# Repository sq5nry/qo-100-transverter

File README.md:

# qo-100-transverter

*[Wersja polska / Polish version](README_PL.md)*

## What it's about
- source-available, hardware and software project of a transverter for the [QO-100](https://amsat-uk.org/satellites/geo/eshail-2/) satellite. The outdoor version takes 1.5 days to assemble starting from bare PCB, bag of parts, and patience.
- complete up and down-converter below 199,99 € : [see the BOM](hw-trv/BOM.md)
- in-fab assembly automation in progress (*v0.3-snapshot*)

## Equipment and skills required
- knack for SMD soldering with stencil and solder paste
- patience for by-hand component placement
- 10x10 cm heat plate and ability to control the temperature profile
- multimeter
- set of fixed attenuators, a variable one and patch cables
- VNA+SA and a signal generator up to 3GHz minimum
- Pluto-like SDR to receive, measure, and generate signals during tests and adjustments
- RF power meter
- 30V 5A lab power supply with over-current protection
- ST-link programmer
- patience for drilling holes in aluminum enclosure
- patience for tapping 3 mm holes
- RF personal protective equipment rated to attenuate 2.4 GHz frequencies

## Features
- QO-100 narrow-band transponder SSB, CW, and Data operation with an HF-VHF transceiver
- ±0.25 ppm reference oscillator stability
- 6W of 2.4GHz output power
- 10m, 6m, 4m, 2m, 70cm bands supported, 5W input power maximum
- 738MHz filtered, receive output for signal supervision
- 25MHz reference oscillator for LNB: injected into the LNB feeder or the shared output
- PTT-over-coax supported
- splash-proof outdoor version

## Block diagram

## Operation

### Prerequisites

- 28V DC power supply offering 1.1A (31W), or
- 13.8V DC at 3.5A and using the Companion Box for voltage boost
- 60cm dish antenna suggested with 5W ERP according to AMSAT guidelines
- standard universal LNB (13/18V), 500mA fused
- standard PTT ground-to-transmit, or
- PTT-over-coax by transceiver or using the Companion Box to mix PTT and RF
- operation from 13.8V (1.1A) directly is possible with lower output power (2W max). Adequate linearity is not guaranteed.

### Basic procedures

1. Configure IF (Intermediate Frequency) corresponding to your transceiver setup using the three-position slide switch to select one of eight possible IF base frequencies.
2. IF can be updated on-the-fly, the change is indicated by a flashing green LED.
3. Connect DC power and PTT signal.
4. Switch on RX pre-amp in your transceiver.
5. Check the position of the received QO-100 mid beacon, adjust it to fall into the middle of the band using REF ADJ control with a small flat-head screwdriver.
6. Set your transceiver output power to 3–5W and adjust TX ATT control so that your signal is at the mid-beacon level. Lower power with a higher TX ATT setting is advised to minimize heat dissipation inside the transverter.

## Schematics

- [v0.3 schematics (current)](hw-trv/sch_v0.3-sh.pdf)
- [v0.2 schematics](https://github.com/sq5nry/qo-100-transverter/blob/77cc88346982ab3cb6913bec3531f18df363a01a/hw-trv/sch_v0.2.pdf) — release presented at [Ham Radio Friedrichshafen 2026](https://www.hamradio-friedrichshafen.com/trade-show-program/exhibitors/exhibitor?id=107515806) in [PZK](https://www.pzk.org.pl/) (Polish Amateur Radio Union) tent

> **⚠️ Note:** do not mount the OCXO subcircuit (error amplifier and heater components, connected via JP5). This circuitry is non-functional in the current release and will be removed in a future revision. The freed board space can instead be used for additional thermal insulation around the TCXO.

## Assembly

### Preparation

Gather all parts from the [BOM](hw-trv/BOM.md) and arrange them on your workbench before starting.
Verify IC orientation markings and keep ESD-sensitive parts (ICs, MOSFETs) in their packaging
until placement.

### Solder paste application

Apply solder paste through the PCB stencil. Two paste options have been tested:

- **Sn63Pb37** (183°C eutectic, e.g. Mechanic XG-50) — recommended; standard SnPb profile,
  widely available, easy to work with.
- **Sn42Bi58** (~138°C eutectic, e.g. ChipQuik SMD291 or Mechanic UV50) — low-melting-point
  alternative; useful if heat-sensitive components are a concern, but requires careful handling
  as bismuth alloys are more brittle and less compatible with lead-containing component finishes.

Clamp the stencil firmly over the PCB, apply paste with a squeegee in a single smooth stroke,
and lift the stencil straight up to avoid smearing. Inspect paste deposits under magnification
before placing components.

### Component placement

Place all SMD components onto the paste deposits. Work from smallest to largest — passives first,
then ICs. Pay close attention to pin-1 orientation on all ICs and polarised components.
QFN packages require careful centring over their pads; the paste surface tension will self-align
them slightly during reflow.

### Reflow

Place the populated PCB on the heat plate. Follow a standard **SnPb reflow profile**:

| Zone | Temperature | Duration |
|------|------------|---------|
| Preheat | 100–150°C | ~60 s |
| Soak | 150–180°C | 60–90 s |
| Reflow (above liquidus) | 183–215°C peak | 30–45 s |
| Cooldown | ramp down | natural |

Use hot air to assist reflow around QFN packages and larger thermal-mass parts (PA, DC-DC
converter). Watch for bridging on fine-pitch ICs.

### Inspection and rework

After reflow and cooldown, inspect all joints under magnification:

- Remove solder bridges with braid or a fine soldering iron tip.
- Add solder to any under-filled joints, particularly on exposed thermal pads of QFN/PQFN
  packages — use a soldering iron with flux through the heat-via holes on the bottom side.
- The bottom-side thermal vias do not need to be flush; they will be covered by thermal pads
  connecting to the heat spreader or enclosure floor.

### Through-hole parts

Solder the 5W power resistor by hand after SMD reflow. Mount the TCVCXO with polyester
tape and foam fitting as described in the enclosure assembly notes.

### EMI shields

The PCB has footprints for SMD metal EMI shields over sensitive sections. Mounting the shield over the IF Unit is important for stability. Shielding the switched-mode power supply section and TCXO is recommended but not critical.

### EMI absorber

Most of enclosure types require absorption foams in PA area to help suppress self-oscillations and minimize parasitic coupling between stages. The amplifier may start self-oscillations at a frequency between 2.2-2.5GHz with full power without the absorber. \
See gallery section for a poor's-man approach.

### PCB cleaning

Wash the assembled PCB thoroughly with isopropanol to remove all flux residues before
proceeding. Flux contamination on the board surface can significantly affect 2.4GHz circuit
behaviour — altering tuning, increasing losses, and making RF adjustments unreliable.
Allow the board to dry completely before applying power.

### Power-up and initial checks

Connect power and PTT cables. Supply 28V with the current limit set to 50mA. Measure the
following test points and verify voltages before proceeding:

1. Check 13V and 5V test points first.
2. If those are correct, verify: 3V (analog), 3V (digital), 3.3V (reference oscillator),
   3V (MCU), 9V, and 1.8V.

If any rail is missing or out of range, do not proceed — investigate before applying full power.

### Firmware

Flash the firmware using **STM32CubeProgrammer** via the ST-LINK interface and the SWD ISP
header. A firmware release binary is provided; to build from source use **STM32CubeIDE**.

After programming, the **PLL LOCK** indicator should illuminate. If it does not, check the
25MHz reference oscillator signal.

### PA bias adjustment

Set the quiescent drain current (Idq) for the 2.4GHz PA stages:

- 1st stage: **15mA**
- 2nd stage: **75mA**

Before adjusting, raise the lab supply's overload protection (current limit) to about
**250mA** so it does not trip during bias trimming.

To measure Idq, cut the respective drain supply PCB trace and insert an ammeter in series or just calculate current delta on the lab supply.
Adjust the bias trimmer for each stage until the target Idq is reached, then bridge the cut
with solder.
Adjust the position of C87 in the PA output circuit for highest stage gain.

### PA gain and output matching

Measure the PA gain and adjust the position of C88 to obtain **28–30dB** gain — slide C88 along the output line toward the thicker section. If that alone does not maximise gain, add 0.8pF in parallel with C88. Do not mount
the low-pass filter (LPF) elements yet — bridge the LPF inductor footprint with a strip of
copper foil instead, so the PA output can be measured without the potentially mismatched filter.

Once the gain is set, mount the LPF inductor and adjust it for a maximum insertion loss of
**1dB at 2.4GHz**.

Set the overload (overcurrent) protection threshold to **1.1A**.

Connect an RF power meter to the 2.4GHz TX output socket and adjust the TX path for **6W**
output across your expected input power range (1–5W).

> **⚠️ Warning:** do not increase input power in an attempt to reach 6W until PA gain is at least 28dB. PA chip will overheat and operate non-linearly. I bricked one PA after overloading its input with just 17dBm.

> **⚠️ Warning:** do not drive the PA past **9..12W** output — exceeding this limit pushes the
> stage into non-linear operation, causing spectral splatter and interference to other users.

> **⚠️ Note:** the PA chip tolerates antenna mismatch well — SWR up to 10:1 on the 2.4GHz
> TX port will not damage it. However, operating with no load connected may cause
> self-oscillation in the 2.2–2.5GHz range; the on-board 1.5A resettable fuse will limit
> the resulting current in that event.

## Circuit description

### Transmit path

The transceiver signal (up to 5W / +37dBm) passes through a variable 35–42dB attenuator,
reducing it to approximately −8dBm at the mixer input. A diode protection limiter with a
clipping level starting softly at +4dBm guards the mixer — this is to limit damage in case you connect 100W for a longer time. Note that sustained high-power overshoots may still damage the PA by exceeding its maximum input level even if the mixer itself survives. \
The signal enters a balanced Gilbert-cell mixer (RFFC2071). The mixer's wideband 4:1 output transformer provides differential symmetry that helps cancel LO leakage, minimising it before the signal
even reaches the downstream filter. Although slightly more expensive than a narrowband balun
chip, the wideband transformer's superior symmetry keeps LO leakage below −32dBc relative
to the upper sideband with only two SAW filters — most critically on the 29MHz band, where
LO leakage lands closest to occupied spectrum. The TX mixer on 10m is intentionally operated at a reduced bias current, which directly reduces LO leakage at its output. \
The output is filtered by a 2.4GHz bandpass filter to further suppress any residual LO leakage and the image frequency. The two TX bandpass filters are inter-stage matched using a parallel 0.8pF capacitor; this matching network optimises power transfer between the filter sections. A driver stage amplifies the signal to +12dBm, followed by a 29dB LDMOS power amplifier — whose input is matched to 50Ω using a short high-impedance transmission line — and a low-pass filter, delivering +38dBm (6W) to
the TX output socket. \
1dB and 3dB fixed attenuation pads improve impedance matching, distribute gain, and improve amplifier stability. Their 50Ω terminations also
provide convenient probe attachment points when measuring gain between individual stages. \
Image attenuation is 40dB on 10m.
Total conversion gain is 2–9dB; about 0.8–4W from the transceiver will produce 6W output.

### Receive path

Both the LNB supply voltage and the 25MHz reference signal (along with its harmonics up to 125MHz) are injected via a bias-T, which must provide sufficient RF isolation across the full 25–738MHz range where these signals share the same junction. The reference signal is low-pass filtered to 125MHz before injection. \
The received 738MHz IF from the LNB passes through a high-pass filter (so as not to hammer the input SAW filters with the reference oscillator) and two cascaded SAW filters centred around 738MHz. Then follows optional splitter to tap IF to the external RX AUX socket. Release v0.2 uses resistive splitter but it's advised to use minimum-loss option as in v0.3-sh. If you don't need the RX AUX output, do not mount the splitter parts.\
From the mixer output the signal passes through a PIN diode switch to the shared TRX socket. The switch's bias-T is built from three inductors in series, chosen to present at least 1kΩ of reactance at
every supported IF band. \
The input attenuator is always present on the RX path — enable the RX preamplifier in your
transceiver to compensate. The receive path does not add amplification (to keep the cost low) and relies on typical LNB signal levels so as not to degrade the SNR with noise from the RX chain. \
On 70cm IF the strongest signals come at S9 level with RX preamp on, mid-beacon is S7.

### Control

The STM32L0 microcontroller configures the RFFC2071 PLL for the RX and TX frequencies corresponding to the IF band selected by the DIP switch. In addition, mixer bias currents ate also configurd per band. On PTT transitions, the logic switches between the TX and RX PLL register banks in the RFFC2071. The PTT signal is a logical OR from the physical PTT line and the coax (PTT-over-coax).

### Indicators

The blue LED indicates that the PLL synthesizer is locked — the MCU has configured the PLL, the 25MHz reference is running, and the LO frequency is being generated. Mixer bias currents are configured according to IF band.

The green LED blinks in RX mode and is lit continuously in TX mode. On startup and on IF band change, it blinks once per IF position number (1–8).

## Jumper configuration

### Jumper reference

| Jumper | Name | Default | Function |
|--------|------|---------|----------|
| JP1 | AUX SEL | Reference | Selects what the RX/REF (AUX) socket outputs: **Reference** (25MHz) or **RX** (738MHz) |
| JP2 | RX SPLIT | no-split | Part of RX split — change together with JP4. Change position only if you want RX in AUX socket. |
| JP4 | RX SPLIT | no-split | Part of RX split — change together with JP2. Change position only if you want RX in AUX socket. |
| JP5 | OVEN | disconnected | Reserved for OCXO option; disabled in v0.2 |
| JP6 | REF ROUTE | AUX path | Routes the 25MHz reference toward the AUX socket (default) or toward the LNB feeder (also check JP7) |
| JP7 | REF TO LNB | open | Solder to mix the 25MHz reference signal into the LNB feeder coax. This jumper enhances signal integrity when the REF signal isn't routed to the LNB feeder. "Open" when you don't want to mix the REF with the LNB feeder, "Connected" to inject the REF into the LNB feeder. |

### Typical usage scenarios

**1. RX/REF (AUX) socket outputs 25MHz reference** *(default — no changes needed)*

Use this to supply 25MHz reference to an external device via the AUX socket.

| JP1 | JP2 | JP4 | JP6 | JP7 |
|-----|-----|-----|-----|-----|
| default (Reference) | default | default | default (AUX path) | open |

---

**2. 25MHz reference injected into LNB feeder cable**

Use this when the LNB is fed its reference via the coax (no separate reference cable needed).

| JP1 | JP2 | JP4 | JP6 | JP7 |
|-----|-----|-----|-----|-----|
| default | default | default | **change (LNB path)** | **solder** |

---

**3. RX signal (738MHz) on AUX socket**

Use this to route the received downconverted signal to an external SDR or receiver via the AUX socket.

| JP1 | JP2 | JP4 | JP6 | JP7 |
|-----|-----|-----|-----|-----|
| **change (RX)** | **change** | **change** | default | open |

---

**4. Reference injected into LNB feeder + RX signal on AUX socket**

Combines use cases 2 and 3: LNB gets its reference via coax, AUX socket carries the RX signal.

| JP1 | JP2 | JP4 | JP6 | JP7 |
|-----|-----|-----|-----|-----|
| **change (RX)** | **change** | **change** | **change (LNB path)** | **solder** |

---

## Gallery

*Click the image to watch the video.*

*Output power — click to watch. 40dB/50W att. + 20dB SMA att (39.5+19,5=59dB at 2.4GHz)*

*Infrared video of the PCB during PA test — passive cooling via aluminum enclosure. Click to watch.*

*Power measurements — click to watch. Heat-pipe directly at PA.*

### Finished units

<table>
<tr>
<td><br><em>cabinet, outdoor classic, outdoor mini, bare bone</em></td>
<td><br><em>cabinet version</em></td>
</tr>
<tr>
<td><br><em>outdoor mini</em></td>
<td><br><em>Companion Box</em></td>
</tr>
<tr>
<td><br><em>cabinet version, back plate</em></td>
<td><br><em>cabinet mini</em></td>
</tr>
</table>

### Enclosure internals

<table>
<tr>
<td><br><em>cabinet version</em></td>
<td><br><em>outdoor classic</em></td>
</tr>
<tr>
<td><br><em>cabinet version</em></td>
<td><br><em>cabinet version</em></td>
</tr>
<tr>
<td><br><em>Companion Box proof-of-concept</em></td>
<td><br><em>outdoor mini</em></td>
</tr>
</table>

### PCB assembly

<table>
<tr>
<td></td>
<td></td>
</tr>
<tr>
<td></td>
<td></td>
</tr>
<tr>
<td></td>
<td></td>
</tr>
<tr>
<td></td>
<td></td>
</tr>
<tr>
<td></td>
<td></td>
</tr>
<tr>
<td></td>
<td></td>
</tr>
<tr>
<td></td>
<td></td>
</tr>
</table>

### PCB details

<table>
<tr>
<td><br><em>2.8GHz low-pass filter</em></td>
<td></td>
</tr>
<tr>
<td></td>
<td></td>
</tr>
<tr>
<td><br><em>replacing IF chip</em></td>
<td></td>
</tr>
</table>

### EMI absorbers

<table>
<tr>
<td></td>
<td></td>
</tr>
<tr>
<td></td>
<td></td>
</tr>
</table>

### Development and testing

<table>
<tr>
<td></td>
<td></td>
</tr>
<tr>
<td></td>
<td></td>
</tr>
<tr>
<td></td>
<td></td>
</tr>
<tr>
<td></td>
<td></td>
</tr>
<tr>
<td></td>
<td><br><em>a cheap C88 (ordinary ceramic instead of ATC porcelain one)</em></td>
</tr>
</table>

### Measurements

<table>
<tr>
<td></td>
<td></td>
</tr>
</table>

## Measurements - TX & RX paths

### TX mixer-to-driver-out, LDMOS gain

<table>
<tr>
<td></td>
<td></td>
</tr>
</table>

### LO, upper sideband, image, and 2nd harmonic levels

<table>
<tr>
<td></td>
<td></td>
</tr>
<tr>
<td></td>
<td></td>
</tr>
</table>

### TRX port

<table>
<tr>
<td align="center"><br><em>TRX port on TX, s11</em></td>
<td align="center"><br><em>TRX port on RX, s11</em></td>
</tr>
</table>

> **⚠️ Note:** TX SWR on 23cm is high. Only RX has been tested and confirmed on this band. Proper TX 23cm testing is in progress — it may work with ALC-limited power from your transceiver.

### RF filtering

*two 739MHz filters cascaded incl. balun loss*

*wideband RX characteristics from F socket to mixer incl. the high-pass filter. No shielding of IF Unit.*

### TCVCXO output spectrum

## Acknowledgements

- **SP5E Krzysztof** — for the original idea and other discussions
- **SQ6QV Tomasz** — for consultation
- **Colleagues from Radio Club in DOK Ursynów** — for countless discussions

## License

All source code, hardware design files, and documentation are publicly available — schematics, PCB layout, and firmware can be freely studied, built, and modified for personal and amateur radio use. This project is dual-licensed by component, and **commercial use of any part of it is not permitted**:

| Component | License |
|---|---|
| Firmware (`src/`, excluding bundled vendor drivers) | [GPL v2 + commercial exception](LICENSE-CODE) |
| Hardware design (`hw-trv/`, `hw-companion-box/`), manual, docs/media | [CC BY-NC-SA 4.0](LICENSE-HARDWARE) |

See [LICENSE](LICENSE) for the full overview. Third-party code bundled
under `src/Drivers/` (ST's STM32 HAL drivers and ARM's CMSIS headers)
keeps its own original license terms.

`src/Core/Src/rffc5071.c`, `src/Core/Src/rffc5071_spi.c`, and associated
headers are derived from [HackRF](https://github.com/greatscottgadgets/hackrf)
by [Great Scott Gadgets](https://greatscottgadgets.com/) and Jared Boone,
licensed under [GPL v2](https://www.gnu.org/licenses/old-licenses/gpl-2.0.html).

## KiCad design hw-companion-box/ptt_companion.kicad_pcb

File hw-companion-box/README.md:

# Companion Box

Auxiliary unit for the QO-100 transverter, providing:

- 13.8V to 28V voltage boost for powering the transverter from a standard 13.8V shack supply
- PTT combiner: mixes PTT signal with RF on the coax line to the transverter

The built-in buzzer sounds an audible alert when the PTT line is unplugged — this is to notify the operator of a disconnected PTT cable before transmitting.

See [schematics](sch_companion_box.pdf) for details.

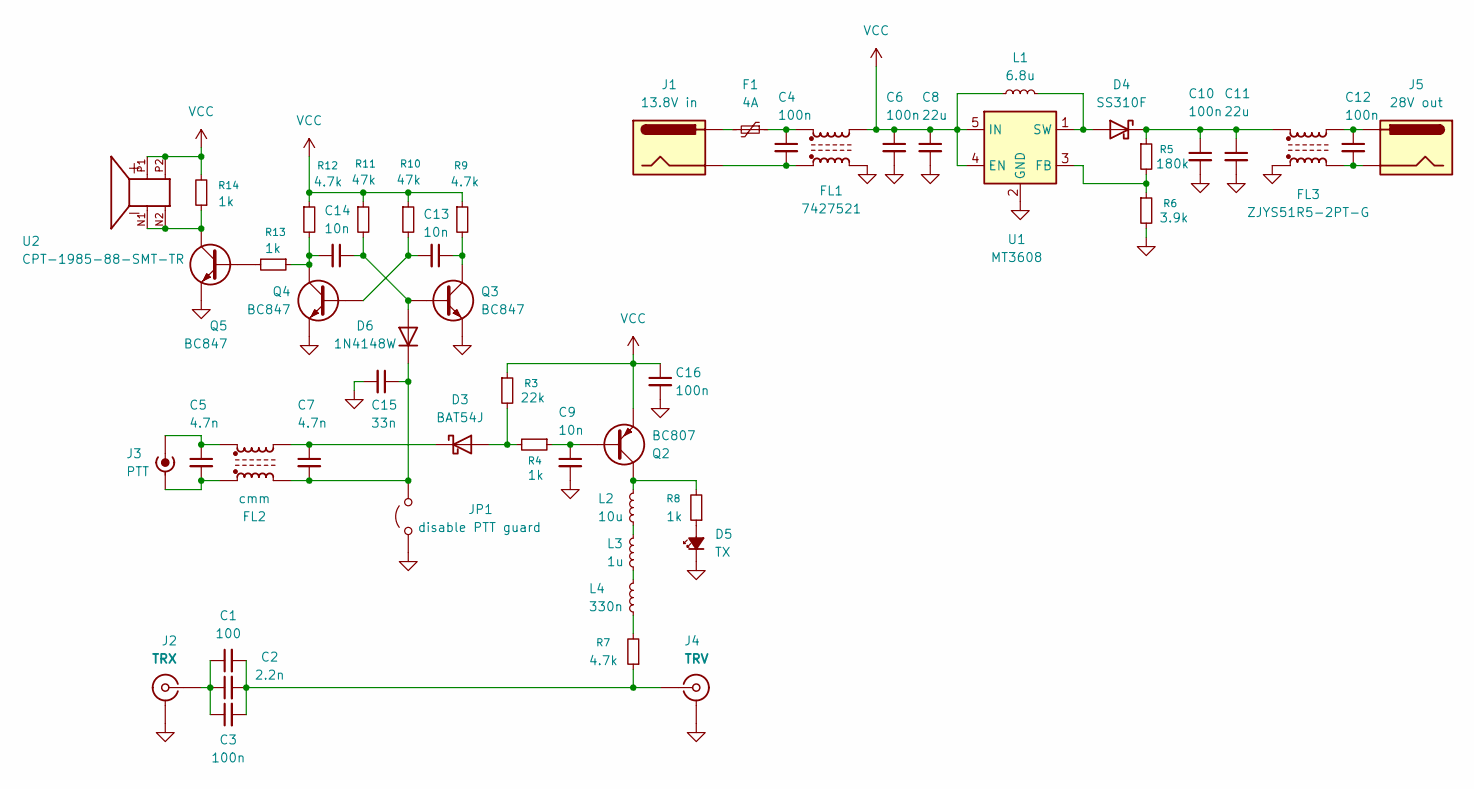
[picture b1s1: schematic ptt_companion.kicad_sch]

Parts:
C1: 100; C_0805_2012Metric_Pad1.18x1.45mm_HandSolder; Voltage 250V
C2: 2.2n; C_0805_2012Metric_Pad1.18x1.45mm_HandSolder; Voltage 250V
C3: 100n; C_0805_2012Metric_Pad1.18x1.45mm_HandSolder; Voltage 250V
C4, C6, C10, C12: 100n; C_0805_2012Metric_Pad1.18x1.45mm_HandSolder
C5, C7: 4.7n; C_0603_1608Metric_Pad1.08x0.95mm_HandSolder
C8, C11: 22u; C_1206_3216Metric_Pad1.33x1.80mm_HandSolder
C9, C13, C14: 10n; C_0603_1608Metric_Pad1.08x0.95mm_HandSolder
C15: 33n; C_0603_1608Metric_Pad1.08x0.95mm_HandSolder
C16: 100n; C_0603_1608Metric_Pad1.08x0.95mm_HandSolder
D3: BAT54J; D_SOD-323F
D4: SS310F; D_SMA_Handsoldering
D5: TX; LED_D5.0mm_Clear
D6: 1N4148W; D_SOD-123
F1: 4A; Fuse_2920_7451Metric_Pad2.10x5.45mm_HandSolder
FL1: 7427521; L_CommonMode_Delevan_4222
FL2: cmm; L_CommonMode_Wurth_WE-CNSW-1206
FL3: ZJYS51R5-2PT-G; L_CommonModeChoke_TDK_ACM7060
J1: 13.8V in; AMASS_XT30U-F_1x02_P5.0mm_Vertical
J2: TRX; MountingHole_5.3mm_M5_Pad_Via
J3: PTT; AMASS_XT30U-F_1x02_P5.0mm_Vertical
J4: TRV; MountingHole_5.3mm_M5_Pad_Via
J5: 28V out; AMASS_XT30U-F_1x02_P5.0mm_Vertical
JP1: disable PTT guard; SolderJumper-2_P1.3mm_Open_TrianglePad1.0x1.5mm
L1: 6.8u; L_Ferrocore_DLG-0403
L2: 10u; L_0805_2012Metric
L3: 1u; L_0805_2012Metric
L4: 330n; L_0805_2012Metric
Q2: BC807; SOT-23
Q3, Q4, Q5: BC847; SOT-23
R3: 22k; R_0603_1608Metric_Pad0.98x0.95mm_HandSolder
R4, R8, R13, R14: 1k; R_0603_1608Metric_Pad0.98x0.95mm_HandSolder
R5: 180k; R_0603_1608Metric_Pad0.98x0.95mm_HandSolder
R6: 3.9k; R_0603_1608Metric_Pad0.98x0.95mm_HandSolder
R7, R9, R12: 4.7k; R_0603_1608Metric_Pad0.98x0.95mm_HandSolder
R10, R11: 47k; R_0603_1608Metric_Pad0.98x0.95mm_HandSolder
U1: MT3608; SOT-23-6
U2: CPT-1985-88-SMT-TR; XDCR_CPT-1985-88-SMT-TR; PARTREV 1.0

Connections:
GND: C6.2, C8.2, C9.2, C10.2, C11.2, C15.2, C16.2, D5.1 (K), FL1.4, FL3.1, J2.2 (Ext), J4.2 (Ext), JP1.1 (A), Q3.2 (E), Q4.2 (E), Q5.2 (E), R6.2, U1.2 (GND)
unnamed: C4.1, F1.1, FL1.1
unnamed: C4.2, FL1.3, J1.2
unnamed: C12.1, FL3.4, J5.1
unnamed: C12.2, FL3.2, J5.2
unnamed: D3.2 (A), R3.2, R4.2
unnamed: C7.1, D3.1 (K), FL2.4
unnamed: D4.2 (A), L1.1, U1.1 (SW)
unnamed: C10.1, C11.1, D4.1 (K), FL3.3, R5.1
unnamed: D5.2 (A), R8.1
unnamed: C14.1, D6.2 (A), Q3.1 (B), R11.2
unnamed: C7.2, C15.1, D6.1 (K), FL2.2, JP1.2 (B)
unnamed: F1.2, J1.1
unnamed: C1.1, C2.1, C3.1, J2.1 (In)
unnamed: C5.2, FL2.1, J3.2 (Ext)
unnamed: C5.1, FL2.3, J3.1 (In)
unnamed: C1.2, C2.2, C3.2, J4.1 (In), R7.1
unnamed: L2.1, L3.2
unnamed: L3.1, L4.2
unnamed: L4.1, R7.2
unnamed: C9.1, Q2.1 (B), R4.1
unnamed: L2.2, Q2.3 (C), R8.2
unnamed: C13.1, Q3.3 (C), R9.2
unnamed: C13.2, Q4.1 (B), R10.2
unnamed: C14.2, Q4.3 (C), R12.2, R13.1
unnamed: Q5.1 (B), R13.2
unnamed: Q5.3 (C), R14.1, U2.N1, U2.N2
unnamed: R5.2, R6.1, U1.3 (FB)
VCC: C6.1, C8.1, C16.1, FL1.2, L1.2, Q2.2 (E), R3.1, R9.1, R10.1, R11.1, R12.1, R14.2, U1.4 (EN), U1.5 (IN), U2.P1, U2.P2

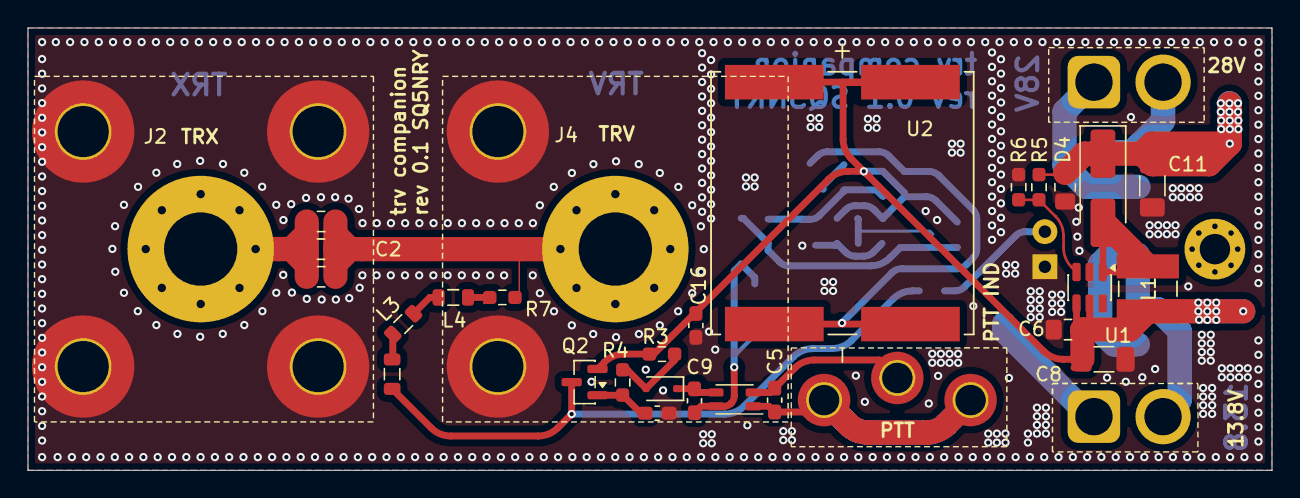
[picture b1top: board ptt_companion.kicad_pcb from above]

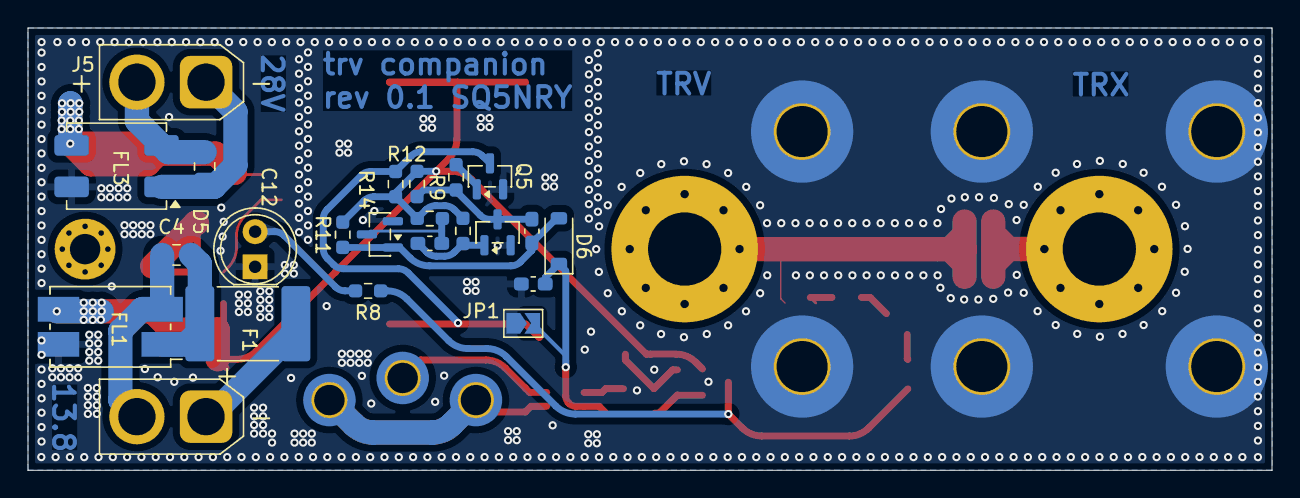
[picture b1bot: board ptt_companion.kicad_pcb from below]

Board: 2 copper layers, 90.0 x 32.0 mm, 51 parts (23 on the bottom side), 29 nets.

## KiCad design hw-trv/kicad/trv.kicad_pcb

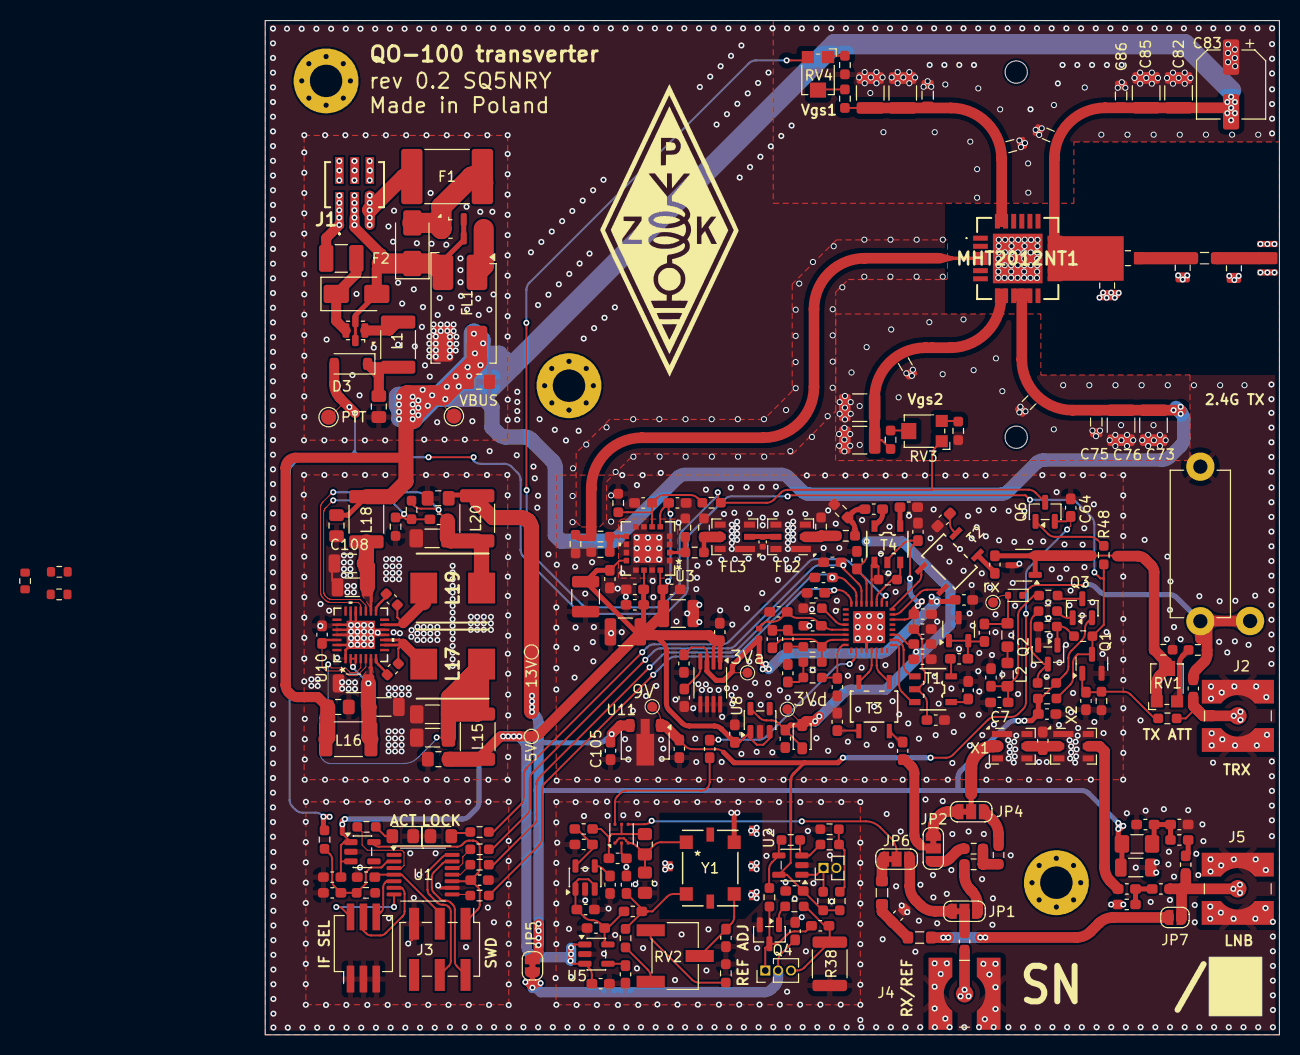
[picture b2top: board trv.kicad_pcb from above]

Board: 2 copper layers, 100.0 x 100.0 mm, 255 parts (0 on the bottom side), 143 nets.

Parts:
3Va, 3Vd, 9V: (no value)
5V, 13V: TestPoint_Pad_D1.0mm
C1, C2: 22n; Filter_Mini-Circuits_FV1206
C3, C4: 1n; C_0805_2012Metric_Pad1.18x1.45mm_HandSolder
C5, C9, C10, C16, C29, C38: 1n; C_0603_1608Metric_Pad1.08x0.95mm_HandSolder
C6, C8, C18, C32, C33, C34, C46, C47, C62, C64, C80: 10n; C_0603_1608Metric_Pad1.08x0.95mm_HandSolder
C7: 100 *; C_0603_1608Metric_Pad1.08x0.95mm_HandSolder
C11, C14, C41, C42, C44, C52, C55, C77, C90, C91, C92, C93, C94, C103, C105: 100n; C_0603_1608Metric_Pad1.08x0.95mm_HandSolder
C12: 180; C_0603_1608Metric_Pad1.08x0.95mm_HandSolder
C13: 8p2; C_0603_1608Metric_Pad1.08x0.95mm_HandSolder
C15, C19: 330; C_0603_1608Metric_Pad1.08x0.95mm_HandSolder
C17, C20, C21, C22, C23, C30, C31: 33; C_0603_1608Metric_Pad1.08x0.95mm_HandSolder
C24, C25, C26, C27, C28, C35, C36, C37, C39, C40, C58: 100; C_0603_1608Metric_Pad1.08x0.95mm_HandSolder
C43: 0; C_0603_1608Metric_Pad1.08x0.95mm_HandSolder
C45: 1; C_0402_1005Metric
C48, C101, C106: 4.7u; C_1206_3216Metric
C49, C54, C60, C69, C72, C73, C82: 10u; C_1210_3225Metric
C50, C57, C61: 470n; C_0603_1608Metric_Pad1.08x0.95mm_HandSolder
C51: 1.8; C_0603_1608Metric_Pad1.08x0.95mm_HandSolder
C53, C65: 3n3; C_0603_1608Metric_Pad1.08x0.95mm_HandSolder
C56: 12; C_0603_1608Metric_Pad1.08x0.95mm_HandSolder
C59, C111: 4.7; C_0603_1608Metric_Pad1.08x0.95mm_HandSolder
C63, C78: 1u; C_0603_1608Metric_Pad1.08x0.95mm_HandSolder
C66, C67, C68, C74, C75, C86, C87: 5.6; L_0805_2012Metric
C70, C71, C76, C85: 100n; C_1210_3225Metric
C79, C104: 2.2u; C_0603_1608Metric_Pad1.08x0.95mm_HandSolder
C81, C84: 470; C_0603_1608Metric_Pad1.08x0.95mm_HandSolder
C83: 220uF; CP_Elec_6.3x5.8
C88: 1.6; C_0805_2012Metric
C89: 4.7; C_0805_2012Metric_Pad1.18x1.45mm_HandSolder
C95: 0.5+1.3; C_0805_2012Metric
C96, C99, C110, C112: 100n; C_0805_2012Metric_Pad1.18x1.45mm_HandSolder
C97, C109, C113: 22u; C_1206_3216Metric_Pad1.33x1.80mm_HandSolder
C98: 1.3; C_0805_2012Metric
C100, C108: 100n; C_1206_3216Metric
C102, C107: 100n; C_0603_1608Metric
D1: SMAJ30CA; D_SMA
D2: SMAJ15CA-TP; D_SMA
D3: BAT54; D_SOD-123
D4: BAR64; D_SOD-523
D5: INFO; LED_0805_2012Metric_Pad1.15x1.40mm_HandSolder
D6, D7: BAV99; SOT-23-3
D8: LOCK; LED_0805_2012Metric_Pad1.15x1.40mm_HandSolder
F1: 1.85A; Fuse_2920_7451Metric_Pad2.10x5.45mm_HandSolder
F2: 100mA; Fuse_1210_3225Metric_Pad1.42x2.65mm_HandSolder
F3: 500mA; Fuse_1206_3216Metric_Pad1.42x1.75mm_HandSolder
FL1: ECMS1V0905-222-R; L_CommonModeChoke_TDK_ACM7060
FL2, FL3: TA0532A; Filter_SAW_Epcos_DCC6C_3x3mm
IC1: RFFC2071TR13
IC2: MHT2012NT1
J1: VCC+PTT; 874370363
J2: TRX; SMA_Wurth_60312102114405_Vertical
J3: SWD ISP; PinHeader_2x03_P2.54mm_Vertical_SMD
J4: RX_OUT / 25M_REF; SMA_Wurth_60312102114405_Vertical
J5: LNB; SMA_Wurth_60312102114405_Vertical
J6: TX; SMA_Wurth_60312102114405_Vertical
JP1, JP2, JP4, JP6: SolderJumper_3_Open; SolderJumper-3_P1.3mm_Bridged12_RoundedPad1.0x1.5mm_NumberL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
JP5: SolderJumper_2_Open; SolderJumper-2_P1.3mm_Bridged_RoundedPad1.0x1.5mm
JP7: SolderJumper_2_Open; SolderJumper-2_P1.3mm_Open_RoundedPad1.0x1.5mm
L1, L15, L18, L20: FB; L_1812_4532Metric_Pad1.30x3.40mm_HandSolder
L2: 0.22u; L_0805_2012Metric_Pad1.05x1.20mm_HandSolder
L3: 1u; L_0805_2012Metric_Pad1.05x1.20mm_HandSolder
L4, L5: FB; L_0402_1005Metric
L6, L21: BK1608HM102TL; L_0603_1608Metric_Pad1.05x0.95mm_HandSolder
L7: 120n; L_0805_2012Metric_Pad1.05x1.20mm_HandSolder
L8: 10n; L_0603_1608Metric_Pad1.05x0.95mm_HandSolder
L9: 180nH; L_0805_2012Metric_Pad1.05x1.20mm_HandSolder
L10: 1u; L_0603_1608Metric_Pad1.05x0.95mm_HandSolder
L11: 220n; L_0603_1608Metric_Pad1.05x0.95mm_HandSolder
L12: FB; L_Walsin_WLFM201209x
L14: 3.3n; L_0805_2012Metric_Pad1.05x1.20mm_HandSolder
L16: FB; Fuse_1812_4532Metric_Pad1.30x3.40mm_HandSolder
L17, L19: 2.2u; INDPM7168X300N
PTT: PTT; TestPoint_Pad_D1.5mm
Q1: BC848; SOT-23
Q2: BC847C; SOT-23
Q3, Q6: BSS84P; SOT-23
Q4: MMBT3904; SOT-23
Q5: MJE122; PinHeader_1x03_P1.27mm_Vertical
R1, R3: 4k7; R_0603_1608Metric_Pad0.98x0.95mm_HandSolder
R2, R8, R33: 100k; R_0603_1608Metric_Pad0.98x0.95mm_HandSolder
R4, R5, R26, R51, R52, R53: 10k; R_0603_1608Metric_Pad0.98x0.95mm_HandSolder
R6, R50, R57: 47k; R_0603_1608Metric_Pad0.98x0.95mm_HandSolder
R7, R10, R36, R48: 1k; R_0603_1608Metric_Pad0.98x0.95mm_HandSolder
R9: 39k; R_0603_1608Metric_Pad0.98x0.95mm_HandSolder
R11: 22k; R_0603_1608Metric_Pad0.98x0.95mm_HandSolder
R12: 56/5W; R_Axial_DIN0614_L14.3mm_D5.7mm_P15.24mm_Horizontal
R13: 1k5; R_0603_1608Metric_Pad0.98x0.95mm_HandSolder
R14, R17: 470; R_0603_1608Metric_Pad0.98x0.95mm_HandSolder
R15, R18, R20: 0; R_0603_1608Metric_Pad0.98x0.95mm_HandSolder
R16, R21, R23: 220; R_0603_1608Metric_Pad0.98x0.95mm_HandSolder
R19: 56; R_0603_1608Metric_Pad0.98x0.95mm_HandSolder
R22: 51k 1%; R_0603_1608Metric_Pad0.98x0.95mm_HandSolder
R24: 6.8k; R_0603_1608Metric_Pad0.98x0.95mm_HandSolder
R25: 15k; R_0603_1608Metric_Pad0.98x0.95mm_HandSolder
R27: 2.7k; R_0603_1608Metric_Pad0.98x0.95mm_HandSolder
R28, R30, R32: 16; R_0603_1608Metric_Pad0.98x0.95mm_HandSolder
R29, R35, R41, R43, R46, R49: 270; R_0603_1608Metric_Pad0.98x0.95mm_HandSolder
R31, R42, R47: 18; R_0603_1608Metric_Pad0.98x0.95mm_HandSolder
R37: 330; R_0603_1608Metric_Pad0.98x0.95mm_HandSolder
R38: 3; R_1812_4532Metric
R39, R40: 2k2; R_0603_1608Metric_Pad0.98x0.95mm_HandSolder
R44, R45: 22k 1%; R_0805_2012Metric_Pad1.20x1.40mm_HandSolder
R54, R55: 4.7k; R_0603_1608Metric_Pad0.98x0.95mm_HandSolder
R56: 560k; R_0603_1608Metric_Pad0.98x0.95mm_HandSolder
RV1: 2k2; Potentiometer_Bourns_TC33X_Vertical
RV2: 2k2; Potentiometer_Bourns_3269W_Vertical
RV3, RV4: 5k; Potentiometer_Bourns_TC33X_Vertical
SW1: SW_DIP_x03; SW_DIP_SPSTx03_Slide_KingTek_DSHP03TJ_W5.25mm_P1.27mm_JPin
T1, T4: ETC1.6-4-2-3TR; ETC1.6-4-2-3TR_MCM
T2, T3: MABACT0039; MABACT0039_MCM
TH1: 10k; PinHeader_1x02_P1.27mm_Vertical
U1: STM32L011D4P6TR; TSSOP-14_4.4x5mm_P0.65mm
U2: LM321; SOT-23-5
U3: SKY66292-11; QFN16_5X5_SKY
U4: 74LVC2G17; Vishay_PowerPAK_SC70-6L_Dual
U5: TPS73633DBVRG4; SOT-23-5
U6: LP2985-18DBVR; SOT-23-5
U7: MIC5219-3.0YMM; MSOP-8_3x3mm_P0.65mm
U8, U9: TLV74130PDBVR; SOT-23-5
U10: MAX20457ATIF/VY+; 21-100130_MXM
U11: L78L09ACUTR; SOT-89-3
VBUS: 28V; TestPoint_Pad_D1.5mm
X1, X2: TA1862A; Filter_SAW_Epcos_DCC6C_3x3mm
Y1: LFTVXO076346 25MHz; LFTVXO076346REEL_IQD-M
rx: RX

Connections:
+1V8: C62.1, L21.1, R44.1, U4.5 (VCC)
+2V8: C11.2, J3.1, U1.10 (VDD), U9.5 (OUT)
+3.3V: C46.2, C94.2, L6.1, U5.5 (OUT), U6.1 (VIN), U6.3 (ON/~OFF)
+3V0/A: 3Va.1, C34.1, C79.2, L4.2, L5.2, U7.3 (OUT)
+3V0/D: 3Vd.1, C18.1, C21.1, C23.2, IC1.19 (DIG_VDD), IC1.29 (RESETX), L12.1
+5V: 5V.1, C49.1, C50.1, C53.1, C54.1, C57.1, C60.1, C61.1, C63.2, C90.2, C91.2, C92.2, C93.2, C96.2, L15.1, U3.5 (VBIAS), U3.12 (VCC3), U3.14 (VCC2), U3.16 (VCC1), U5.1 (IN), U5.3 (EN), U7.1 (EN), U7.2 (IN), U8.1 (IN), U8.3 (EN), U9.1 (IN), U9.3 (EN)
+9V: 9V.1, C41.1, C64.1, C103.2, Q6.2 (S), R24.2, R25.2, U2.5 (V+), U11.1 (OUT)
+13V: 13V.1, C6.1, C48.2, C105.2, C112.2, F3.1, JP5.2 (B), L20.2, Q3.2 (S), R3.1, R6.1, U11.3 (IN)
/ANA_VDD2: C28.2, C31.1, C33.1, C35.2, IC1.22 (ANA_VDD2), L5.1, T1.2, T4.2
/LNB_REF: JP6.2 (C), U4.4
/PLL_REF: C29.1, U4.6
/RFFC_ENX: C22.2, IC1.30 (ENX), R20.1
/RFFC_SCLK: C20.2, IC1.31 (SCLK), R18.1
/RFFC_SDATA: C17.2, IC1.32 (SDATA), R15.1
/SUPSW: C100.2, C101.2, L16.2, U10.2 (EN2), U10.3 (EN1), U10.6 (SUPSW1)
/SWCLK: J3.4, U1.14 (PA14)
/SWDIO: J3.2, U1.13 (PA13)
//PA_ENABLE: D3.2 (A), PTT.1, Q1.3 (C), R3.2, R4.1, R8.1, R48.2
GND: C3.1, C4.1, C5.2, C6.2, C7.2, C8.2, C9.1, C11.1, C14.1, C15.2, C17.1, C18.2, C19.2, C20.1, C21.2, C22.1, C23.1, C25.2, C27.2, C28.1, C30.2, C31.2, C32.2, C33.2, C34.2, C35.1, C37.2, C39.2, C41.2, C43.2, C44.2, C45.2, C46.1, C47.1, C48.1, C49.2, C50.2, C52.1, C53.2, C54.2, C55.1, C56.2, C57.2, C58.1, C60.2, C61.2, C62.2, C63.1, C64.2, C65.2, C66.2, C67.2, C68.2, C69.2, C70.2, C71.2, C72.2, C73.2, C74.1, C75.1, C76.2, C77.1, C78.1, C79.1, C80.1, C81.1, C82.2, C83.1, C84.1, C85.2, C86.1, C87.1, C88.1, C90.1, C91.1, C92.1, C93.1, C94.1, C95.1, C96.1, C97.1, C98.1, C99.1, C100.1, C101.1, C103.1, C104.1, C105.1, C106.1, C108.1, C109.1, C110.1, C112.1, C113.1, D5.1 (K), D6.3 (K), D7.3 (K), D8.1 (K), FL1.4, FL2.1 (GND), FL2.3 (GND), FL2.4 (GND), FL2.6 (GND), FL3.1 (GND), FL3.3 (GND), FL3.4 (GND), FL3.6 (GND), IC1.12 (TM), IC1.33 (GND), IC2.25 (EP), J2.2 (Ext), J3.5, J4.2 (Ext), J5.2 (Ext), J6.2 (Ext), L8.1, Q1.2 (E), Q2.2 (E), Q4.2 (E), R2.2, R5.2, R9.2, R12.1, R19.2, R22.1, R26.1, R29.1, R35.1, R38.2, R40.1, R41.1, R43.1, R45.2, R46.1, R49.1, R51.2, R52.1, R53.1, R57.2, SW1.1, SW1.2, SW1.3, TH1.2, U1.9 (VSS), U2.2 (V-), U3.1 (GND), U3.3 (GND), U3.4 (GND), U3.7 (GND), U3.8 (GND), U3.10 (GND), U3.11 (GND), U3.13 (GND), U3.15 (GND), U3.17 (EPAD), U4.2 (GND), U5.2 (GND), U6.2 (GND), U7.5 (GND), U7.6 (GND), U7.7 (GND), U7.8 (GND), U8.2 (GND), U9.2 (GND), U10.1 (PGND), U10.11 (PGND1), U10.12 (PGND2), U10.19 (PGND), U10.20 (PGND), U10.23 (PGND), U10.24 (PGND), U10.25 (AGND), U10.27 (EXTVCC), U10.29 (EPAD), U11.2 (GND), X1.1 (GND), X1.3 (GND), X1.4 (GND), X1.6 (GND), X2.1 (GND), X2.3 (GND), X2.4 (GND), X2.6 (GND), Y1.2 (GND)
unnamed: C1.3, FL1.1
unnamed: C2.1, L1.1
unnamed: C7.1, C8.1, L2.1, R10.2
unnamed: C12.2, R11.1
unnamed: C15.1, R14.1, R17.2
unnamed: C24.1, T2.3
unnamed: C25.1, T2.1
unnamed: C26.1, T1.5
unnamed: C27.1, T1.4
unnamed: C36.1, T3.4
unnamed: C37.1, T3.5
unnamed: C39.1, T4.4
unnamed: C40.1, T4.5
unnamed: C40.2, R29.2, R31.1
unnamed: C51.1, C59.2, L8.2
unnamed: C55.2, C58.2, F3.2, L10.1
unnamed: C56.1, L7.2, L9.1
unnamed: C88.2, C89.2
unnamed: C89.1, C95.2, L14.1
unnamed: C102.2, L17.2, U10.9 (LX1), U10.10 (LX1)
unnamed: C1.2, C2.2, D1.1 (A1), D2.2 (A2), FL1.2, J1.2
unnamed: C1.1, D1.2 (A2), F1.2
unnamed: C2.3, D2.1 (A1), F2.2
unnamed: C3.2, D3.1 (K), L1.2
unnamed: C16.1, D4.2 (A), L3.1, rx.1
unnamed: C10.2, D4.1 (K), R12.2, R13.1
unnamed: D5.2 (A), R16.1
unnamed: C24.2, D6.1 (K), D6.2 (A), R19.1, RV1.1, RV1.2
unnamed: C16.2, C26.2, D7.1 (K), D7.2 (A)
unnamed: D8.2 (A), R21.2
unnamed: FL2.2 (IN), R31.2, R35.2
unnamed: C45.1, FL2.5 (OUT), FL3.2 (IN)
unnamed: FL3.5 (OUT), R41.2, R42.1
unnamed: IC1.13 (MIX1_IPN), T3.1
unnamed: IC1.14 (MIX1_IPP), T3.3
unnamed: IC1.17 (MIX1_OPN), T1.3
unnamed: IC1.18 (MIX1_OPP), T1.1
unnamed: IC1.24 (MIX2_IPN), T2.5
unnamed: IC1.23 (MIX2_IPP), T2.4
unnamed: IC1.27 (MIX2_OPN), R23.1, T4.3
unnamed: IC1.28 (MIX2_OPP), R23.2, T4.1
unnamed: C30.1, C32.1, IC1.5 (ANA_VDD1), L4.1
unnamed: IC1.26 (GPO4/LD/DO), R21.1
unnamed: C12.1, C13.1, IC1.6 (LFILT1)
unnamed: C13.2, IC1.7 (LFILT2), R11.2, R14.2
unnamed: C19.1, IC1.8 (LFILT3), R17.1
unnamed: C29.2, IC1.10 (REF_IN)
unnamed: IC1.4 (REXT), R22.2
unnamed: IC2.3 (RFIN_1), IC2.4 (RFIN_2), R47.2, R49.2
unnamed: IC2.13 (N/C), IC2.14 (N/C), IC2.15 (VDS2_1)
unnamed: C66.1, C67.1, C71.1, C72.1, IC2.23 (N/C), IC2.24 (VGS1), R54.2
unnamed: C68.1, C69.1, C70.1, IC2.7 (N/C), IC2.8 (VGS2), R55.2
unnamed: F2.1, J1.1
unnamed: F1.1, J1.3
unnamed: C10.1, J2.1 (In), R1.1
unnamed: C14.2, J3.3, U1.4 (NRST)
unnamed: C38.2, J4.1 (In)
unnamed: C59.1, J5.1 (In), JP7.2 (B), L11.2
unnamed: C98.2, J6.1 (In), L14.2
unnamed: JP1.1 (A), JP6.3 (B)
unnamed: JP1.3 (B), R30.2
unnamed: C38.1, JP1.2 (C)
unnamed: JP2.1 (A), JP4.1 (A)
unnamed: JP2.3 (B), R28.1
unnamed: C36.2, JP2.2 (C)
unnamed: JP4.3 (B), R32.1
unnamed: JP4.2 (C), X1.2 (IN)
unnamed: C44.1, JP5.1 (A), Q5.2 (C)
unnamed: JP6.1 (A), L7.1
unnamed: JP7.1 (A), L9.2
unnamed: L2.2, L3.2
unnamed: L10.2, L11.1
unnamed: C5.1, Q1.1 (B), R1.2, R2.1
unnamed: Q2.1 (B), R4.2, R5.1
unnamed: Q2.3 (C), R6.2, R7.2
unnamed: Q3.3 (D), R10.1
unnamed: Q3.1 (G), R7.1
unnamed: Q4.1 (B), R37.2
unnamed: C42.1, Q4.3 (C), Q5.1 (B), R36.2
unnamed: C42.2, Q5.3 (E), R37.1, R38.1
unnamed: Q6.3 (D), R50.1, RV3.1, RV4.3
unnamed: Q6.1 (G), R48.1
unnamed: R13.2, RV1.3
unnamed: R25.1, R26.2, R27.1
unnamed: R28.2, R30.1, R32.2
unnamed: R33.2, R36.1, U2.4
unnamed: R39.1, RV2.3
unnamed: R40.2, RV2.1
unnamed: R52.2, RV3.3
unnamed: R53.2, RV4.1
unnamed: R54.1, RV4.2
unnamed: R55.1, RV3.2
unnamed: SW1.4, U1.5 (PA0)
unnamed: SW1.5, U1.6 (PA1)
unnamed: SW1.6, U1.7 (PA4)
unnamed: R15.2, U1.8 (PA7)
unnamed: R18.2, U1.11 (PA9)
unnamed: R20.2, U1.12 (PA10)
unnamed: C9.2, R8.2, R9.1, U1.2 (PC14)
unnamed: R16.2, U1.3 (PC15)
unnamed: R24.1, TH1.1, U2.1 (+)
unnamed: R27.2, R33.1, U2.3 (-)
unnamed: C65.1, R50.2, R51.1, U3.6 (PAEN)
unnamed: R42.2, R43.2, U3.2 (RFIN)
unnamed: R46.2, R47.1, U3.9 (RFOUT)
unnamed: C80.2, U5.4 (NR)
unnamed: C81.2, U6.4 (BP)
unnamed: C77.2, L21.2, U6.5 (VOUT)
unnamed: C84.2, U7.4 (BP)
unnamed: C78.2, L12.2, U8.5 (OUT)
unnamed: C104.2, U10.5 (FB1), U10.26 (BIAS)
unnamed: C102.1, U10.7 (BST1)
unnamed: C107.1, U10.15 (BST2)
unnamed: C111.1, R56.2, R57.1, U10.17 (FB2)
unnamed: C107.2, L19.1, U10.13 (LX2)
unnamed: C97.2, C113.2, L15.2, L17.1, U10.4 (OUT1)
unnamed: C109.2, C111.2, L19.2, L20.1, R56.1, U10.18 (OUT2)
unnamed: C106.2, C108.2, L18.1, U10.16 (SUPSW2)
unnamed: C43.1, X1.5 (OUT), X2.2 (IN)
unnamed: C51.2, X2.5 (OUT)
unnamed: R44.2, R45.1, U4.1, U4.3, Y1.4 (OUT)
unnamed: C47.2, RV2.2, Y1.1 (VC)
unnamed: C52.2, L6.2, R39.2, Y1.5 (VS)
VBUS: C4.2, C73.1, C74.2, C75.2, C76.1, C82.1, C83.2, C85.1, C86.2, C87.2, C99.2, C110.2, FL1.3, IC2.9 (N/C), IC2.10 (VDS1), IC2.11 (N/C), IC2.16 (VDS2_2), IC2.17 (N/C), IC2.18 (N/C), L16.1, L18.2, VBUS.1

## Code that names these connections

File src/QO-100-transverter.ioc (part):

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Mcu.Name=STM32L011D(3-4)Px
Mcu.Package=TSSOP14
Mcu.UserName=STM32L011D4Px
PA0-CK_IN.GPIOParameters=GPIO_PuPd,GPIO_Label
PA0-CK_IN.GPIO_Label=BANDSWITCH_1
PA0-CK_IN.GPIO_PuPd=GPIO_PULLUP
PA0-CK_IN.Signal=GPIO_Input
PA1.GPIOParameters=GPIO_PuPd,GPIO_Label
PA1.GPIO_Label=BANDSWITCH_2
PA1.GPIO_PuPd=GPIO_PULLUP
PA1.Signal=GPIO_Input
PA10.Signal=GPIO_Output
PA13.Mode=Serial_Wire
PA13.Signal=SYS_SWDIO
PA14.Mode=Serial_Wire
PA14.Signal=SYS_SWCLK
PA4.GPIOParameters=GPIO_PuPd,GPIO_Label
PA4.GPIO_Label=BANDSWITCH_3
PA4.GPIO_PuPd=GPIO_PULLUP
PA4.Signal=GPIO_Input
PA7.Signal=GPIO_Output
PA9.Signal=GPIO_Output
PC14-OSC32_IN.Signal=GPIO_Input
PC15-OSC32_OUT.Signal=GPIO_Output
RCC.HSE_VALUE=8000000
RCC.SYSCLKFreq_VALUE=2097000
board=custom

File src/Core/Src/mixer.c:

/*
 * Copyright 2017-2022 Great Scott Gadgets <info@greatscottgadgets.com>
 *
 * This file is part of HackRF.
 *
 * This program is free software; you can redistribute it and/or modify
 * it under the terms of the GNU General Public License as published by
 * the Free Software Foundation; either version 2, or (at your option)
 * any later version.
 *
 * This program is distributed in the hope that it will be useful,
 * but WITHOUT ANY WARRANTY; without even the implied warranty of
 * MERCHANTABILITY or FITNESS FOR A PARTICULAR PURPOSE.  See the
 * GNU General Public License for more details.
 *
 * You should have received a copy of the GNU General Public License
 * along with this program; see the file COPYING.  If not, write to
 * the Free Software Foundation, Inc., 51 Franklin Street,
 * Boston, MA 02110-1301, USA.
 */

#include "mixer.h"
#include "rffc5071.h"
#include "rffc5071_spi.h"
#include "stm32l0xx_hal.h"
#include "main.h"

/* RFFC5071 GPIO serial interface PinMux */
// clang-format off

const rffc5071_spi_config_t rffc5071_spi_config = {
		.gpio_select_port = RFFC_Port, .gpio_select_pin = RFFC_ENX_Pin,
		.gpio_clock_port = RFFC_Port, .gpio_clock_pin = RFFC_SCLK_Pin,
		.gpio_data_port = RFFC_Port, .gpio_data_pin = RFFC_SDATA_Pin,
};

spi_bus_t spi_bus_rffc5071 = {
		.config = &rffc5071_spi_config,
		.start = rffc5071_spi_start,
		.transfer = rffc5071_spi_transfer,
		.transfer_gather = rffc5071_spi_transfer_gather,
};

rffc5071_driver_t mixer = {
		.bus = &spi_bus_rffc5071,
};


rffc5071_driver_t* mixer_bus_setup() {
	spi_bus_start(&spi_bus_rffc5071, &rffc5071_spi_config);
	return &mixer;
}

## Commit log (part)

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2026-06-30 code upload
2026-06-30 removed backup file
2026-06-30 add circuit description section to README
2026-06-30 block diagram updated readme updated
2026-06-30 readme updates

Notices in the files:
README.md:
Hardware: CC BY-NC-SA 4.0
Firmware: GPL v2
